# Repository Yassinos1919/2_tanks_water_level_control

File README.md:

# Two-Tank Liquid Level Controller 🎛️💧

An automated control system that maintains constant liquid levels in a coupled two-tank setup using PID control, Arduino, and LabVIEW.

## 📋 Project Overview

This project implements an industrial-grade liquid level control system for a coupled two-tank configuration. The system uses PID control to maintain a desired water level in the second tank, demonstrating fundamental control theory principles with practical hardware implementation.

**Key Features:**
- ✅ Real-time PID level control
- ✅ Custom PCB design
- ✅ LabVIEW monitoring interface
- ✅ Ultrasonic sensor integration
- ✅ PWM pump control
- ✅ Remote parameter tuning

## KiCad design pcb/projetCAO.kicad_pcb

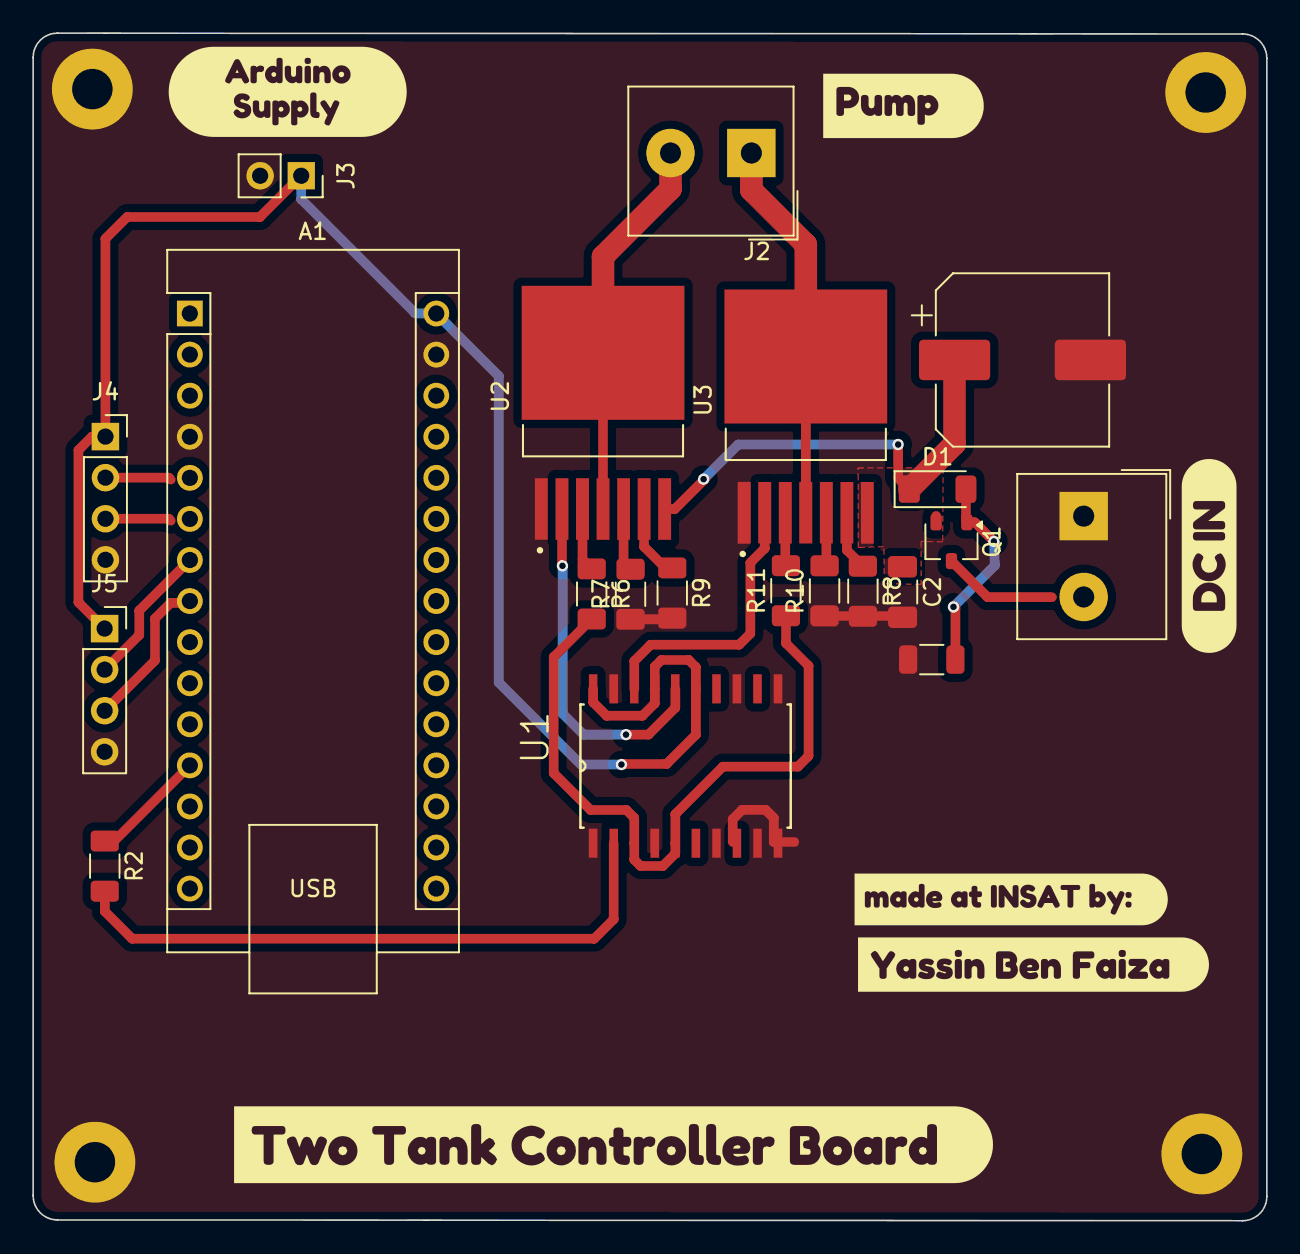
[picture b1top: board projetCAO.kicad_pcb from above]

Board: 2 copper layers, 76.3 x 73.4 mm, 31 parts (0 on the bottom side), 22 nets.

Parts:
A1: Arduino_Nano_v3.x; Arduino_Nano
C1: 470u; CP_Elec_10x10.5
C2: 100n; C_1206_3216Metric_Pad1.33x1.80mm_HandSolder
D1: BZV55B10; D_MiniMELF
H1, H2, H3, H4: MountingHole_Pad; MountingHole_2.5mm_Pad
J1: 12V input; Altech_AK100_1x02_P5.00mm
J2: OUT; Altech_AK100_1x02_P5.00mm
J3: Alimentation; PinSocket_1x02_P2.54mm_Vertical
J4: Ultrasonic1; PinSocket_1x04_P2.54mm_Vertical
J5: Ultrasonic2; PinSocket_1x04_P2.54mm_Vertical
Q1: AO3401A; SOT-23W
R1: 10K; R_1206_3216Metric
R2, R6, R11: 10K; R_1206_3216Metric_Pad1.30x1.75mm_HandSolder
R7, R8, R9, R10: 4.7K; R_1206_3216Metric_Pad1.30x1.75mm_HandSolder
U1: 74HC244; SOIC127P1032X265-20N
U2, U3: BTS7960B; DPAK127P1490X440-8N
kibuzzard-68C5A47A: G***; kibuzzard-68C5A47A
kibuzzard-681AAFCF: G***; kibuzzard-681AAFCF
kibuzzard-681AB00E: G***; kibuzzard-681AB00E
kibuzzard-681AB02C: G***; kibuzzard-681AB02C
kibuzzard-681AC34F: G***; kibuzzard-681AC34F
kibuzzard-67925609: G***; kibuzzard-67925609

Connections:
ECHO1: A1.6 (D3), J4.3
ECHO2: A1.8 (D5), J5.3
EN: R6.2, R11.1, U1.3 (2Y0), U1.5 (2Y1)
GND: A1.4 (GND), A1.29 (GND), C1.2, C2.2, H1.1, H2.1, H3.1, H4.1, J1.1, J3.2, J4.4, J5.4, R1.2, R7.1, R8.2, R9.2, R10.1, U1.1 (1OE), U1.4 (1A1), U1.7 (2Y2), U1.9 (2Y3), U1.10 (GND), U1.11 (2A3), U1.13 (2A2), U1.19 (2OE), U2.1 (GND), U3.1 (GND)
unnamed: D1.2 (A), Q1.1 (G), R1.1
unnamed: J1.2, Q1.3 (D)
unnamed: J2.1, U3.4 (OUT), U3.8 (OUT)
unnamed: J2.2, U2.4 (OUT), U2.8 (OUT)
unnamed: R2.2, U1.2 (1A0)
unnamed: R6.1, U2.3 (INH)
unnamed: R9.1, U2.6 (IS)
unnamed: R7.2, U2.5 (SR)
unnamed: R11.2, U3.3 (INH)
unnamed: R8.1, U3.6 (IS)
unnamed: R10.2, U3.5 (SR)
OUT1: U1.18 (1Y0), U3.2 (IN)
OUT2: U1.16 (1Y1), U2.2 (IN)
RPWM1: A1.12 (D9), R2.1
Supply: C1.1, C2.1, D1.1 (K), Q1.2 (S), U2.7 (VS), U3.7 (VS)
TRIG1: A1.5 (D2), J4.2
TRIG2: A1.7 (D4), J5.2
VCC: A1.30 (VIN), J3.1, J4.1, J5.1, U1.15 (2A1), U1.17 (2A0), U1.20 (VCC)

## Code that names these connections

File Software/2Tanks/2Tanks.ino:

#include <PID_v1.h>

// Tank heights
const float tankHeight1 = 13.0;
const float tankHeight2 = 15.0;

// Ultrasonic pins
const int trig1 = 2, echo1 = 3; // Tank 1
const int trig2 = 4, echo2 = 5; // Tank 2

// Pump control
const int pumpPWM = 9;

// PID variables
double setpoint = 6;
double input, output;
double Kp = 100, Ki = 1, Kd = 0.1;

// PID setup
PID myPID(&input, &output, &setpoint, Kp, Ki, Kd, DIRECT);

void setup() {
  Serial.begin(115200);

  pinMode(trig1, OUTPUT);
  pinMode(echo1, INPUT);
  pinMode(trig2, OUTPUT);
  pinMode(echo2, INPUT);
  pinMode(pumpPWM, OUTPUT);

  myPID.SetMode(AUTOMATIC);
  myPID.SetOutputLimits(0, 255); // PWM range
}

float getLevel(int trigPin, int echoPin, float tankHeight) {
  digitalWrite(trigPin, LOW);
  delayMicroseconds(2);
  digitalWrite(trigPin, HIGH);
  delayMicroseconds(10);
  digitalWrite(trigPin, LOW);

  long duration = pulseIn(echoPin, HIGH, 30000);
  float distance = duration * 0.034 / 2.0;

  float level = tankHeight - distance;
  if (level < 0) level = 0;
  if (level > tankHeight) level = tankHeight;
  return level;
}

void loop() {
  // Read tank levels
  float tank1Level = getLevel(trig1, echo1, tankHeight1);
  input = getLevel(trig2, echo2, tankHeight2);

  // Compute PID
  myPID.Compute();
  analogWrite(pumpPWM, (int)output);

  // --- Serial Receive Format: "Kp,Ki,Kd,Setpoint\n" ---
  if (Serial.available()) {
    String s = Serial.readStringUntil('\n');
    s.trim(); // Remove trailing newline
    int idx1 = s.indexOf(',');
    int idx2 = s.indexOf(',', idx1 + 1);
    int idx3 = s.indexOf(',', idx2 + 1);

    if (idx1 > 0 && idx2 > idx1 && idx3 > idx2) {
      // Extract values
      Kp = s.substring(0, idx1).toFloat();
      Ki = s.substring(idx1 + 1, idx2).toFloat();
      Kd = s.substring(idx2 + 1, idx3).toFloat();
      setpoint = s.substring(idx3 + 1).toFloat();

      // Update PID tunings
      myPID.SetTunings(Kp, Ki, Kd);
    }
  }

  // --- Send to LabVIEW ---
  Serial.print(tank1Level); Serial.print(",");
  Serial.print(input); Serial.print(",");
  Serial.println(output);

  delay(500);
}

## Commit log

2025-11-09 project added
2025-11-09 Rename Capture d'écran 2025-11-09 123720.png to prototype
